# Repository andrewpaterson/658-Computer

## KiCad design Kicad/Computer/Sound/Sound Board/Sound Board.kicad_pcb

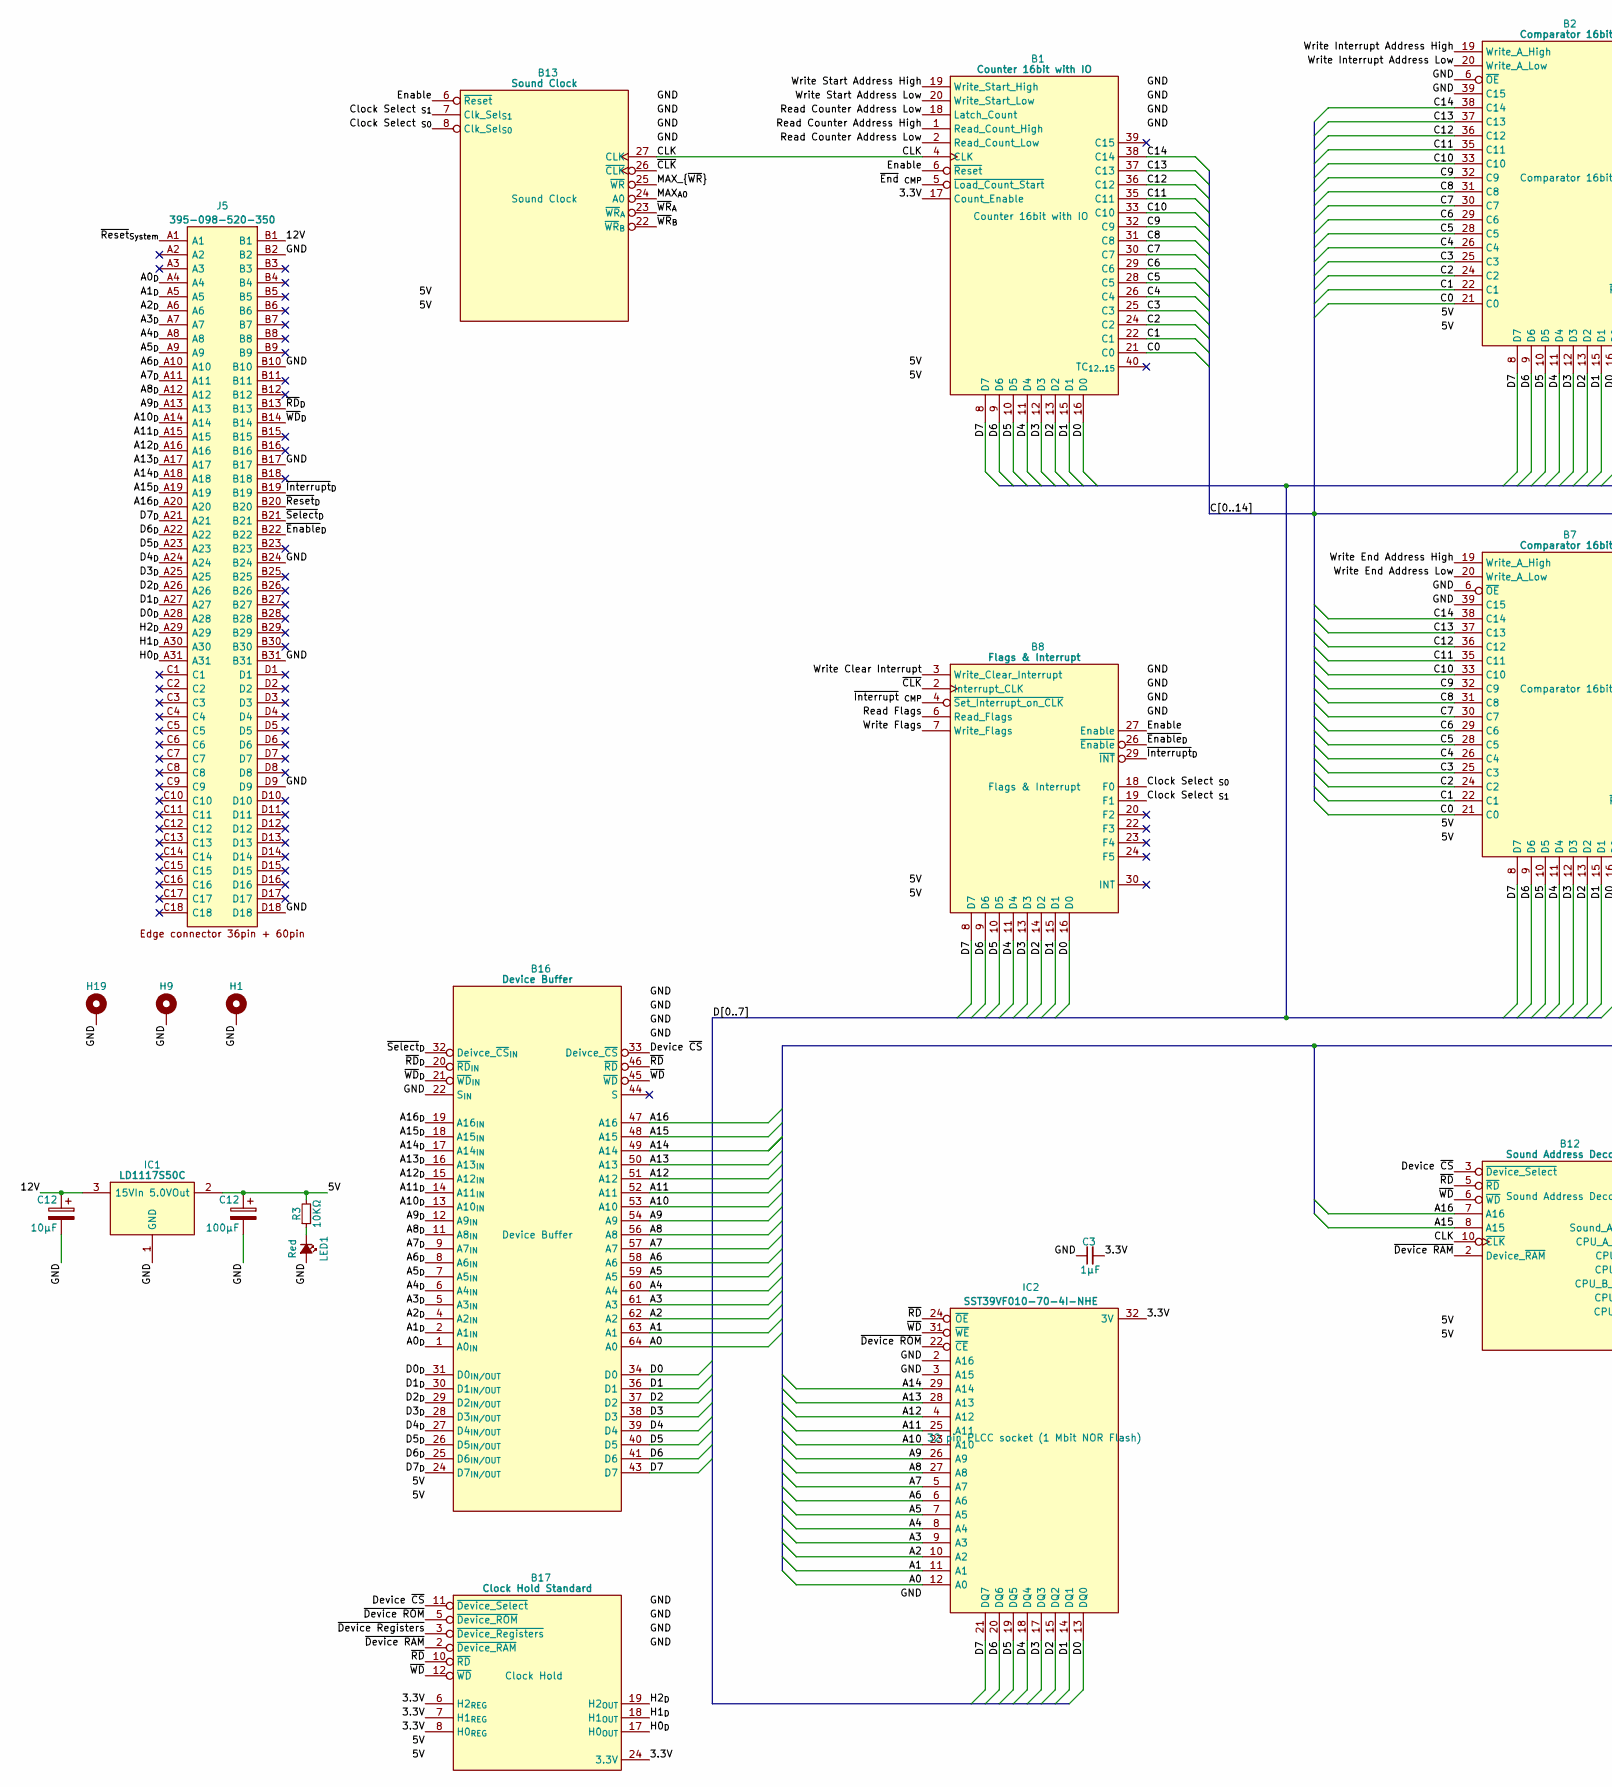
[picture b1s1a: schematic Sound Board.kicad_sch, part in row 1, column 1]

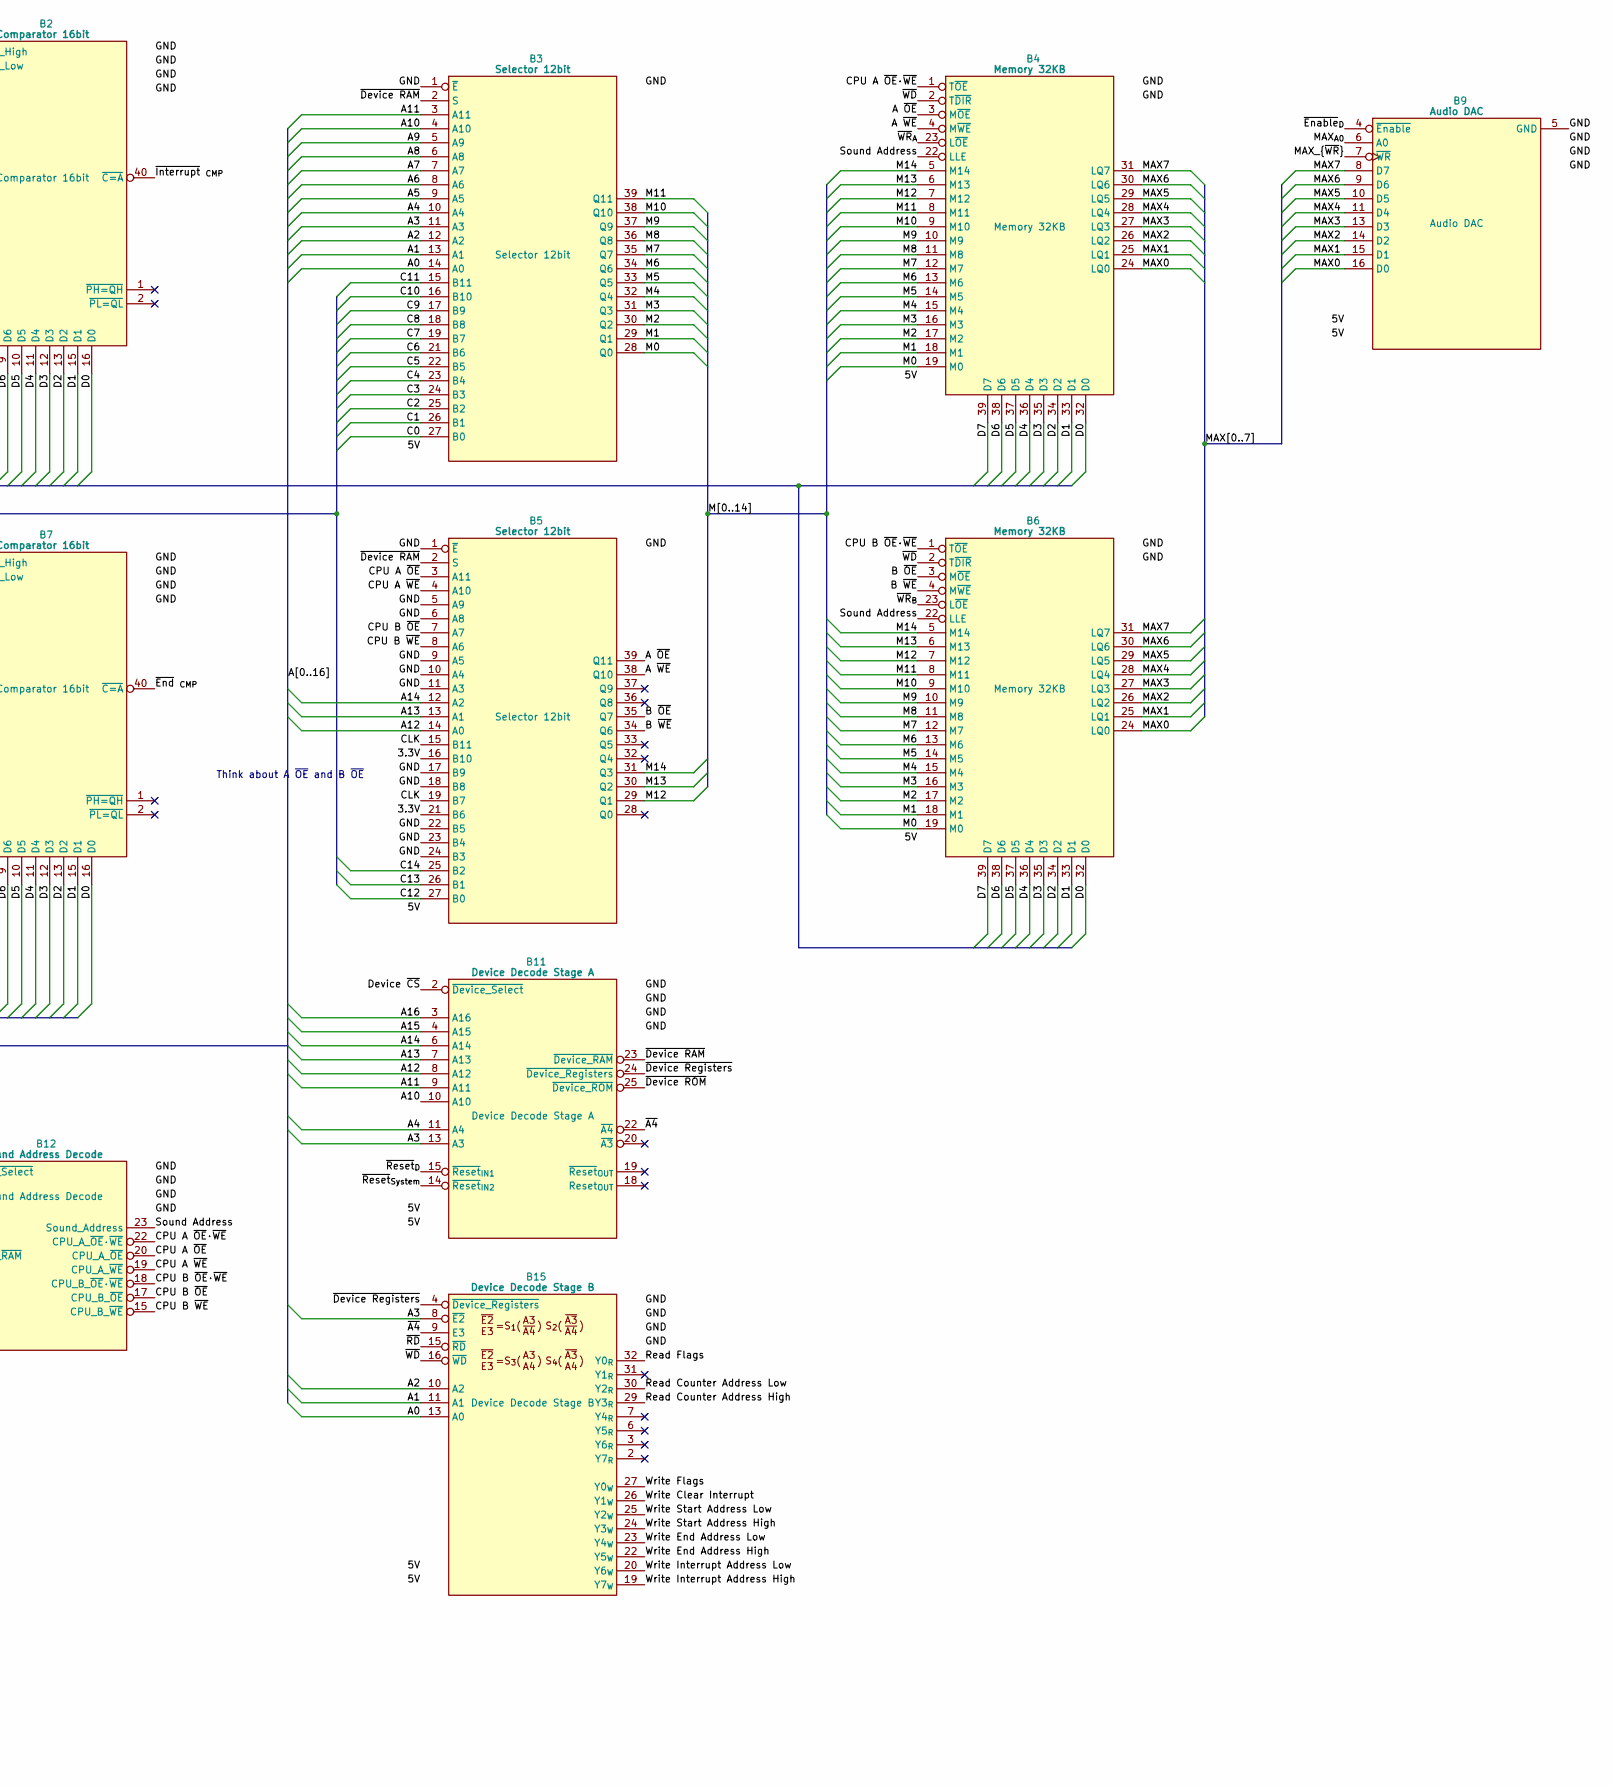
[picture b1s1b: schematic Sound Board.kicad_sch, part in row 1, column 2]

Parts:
B1: Counter 16bit with IO; HCP65_Counter_16bit_DIO
B2, B7: Comparator 16bit; HCP65_Comparator_16bit
B3, B5: Selector 12bit; HCP65_Selector_12bit
B4, B6: Memory 32KB; HCP65_Memory_32KB_With_Latch
B8: Flags & Interrupt; HCP65_Flags_Interrupt
B9: Audio DAC; HCP65_Audio_DAC
B11: Device Decode Stage A; HCP65_Device_Decode_Stage_A
B12: Sound Address Decode; HCP65_Sound_Address_Decode
B13: Sound Clock; HCP65_Sound_Clock
B15: Device Decode Stage B; HCP65_Device_Decode_Stage_B
B16: Device Buffer; HCP65_Device_Buffer
B17: Clock Hold Standard; HCP65_Clock_Hold_Standard
C3: 1μF; C_0805
C12: 10μF; CP_Radial_D4.0mm_P2.00mm
H1, H9, H19: MountingHole_Pad; HCP65_MountingHole_M3_
IC1: LD1117S50C; LD1117S33C; Manufacturer_Part_Number LD1117S50C
IC2: SST39VF010-70-4I-NHE; 5408803224008; Manufacturer_Part_Number SST39VF010-70-4I-NHE
J5: 395-098-520-350; 98pin Edge Connector; Manufacturer_Part_Number 395-098-520-350; Mouser Part Number 587-395-098-520-350
LED1: Red; LED_D5.0mm
R3: 10KΩ; R_0805

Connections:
/3.3V: B1.17 (Count_Enable), B5.16 (B10), B5.21 (B6), B17.6 (H2_{REG}), B17.7 (H1_{REG}), B17.8 (H0_{REG}), B17.24 (3.3V), C3.2, IC2.32 (3V)
/5V: B1.3 (5V), B1.23 (5V), B2.3 (5V), B2.23 (5V), B3.20 (5V), B4.20 (5V), B5.20 (5V), B6.20 (5V), B7.3 (5V), B7.23 (5V), B8.1 (5V), B8.17 (5V), B9.1 (5V), B9.17 (5V), B11.1 (5V), B11.17 (5V), B12.1 (5V), B12.13 (5V), B13.1 (5V), B13.17 (5V), B15.1 (5V), B15.17 (5V), B16.3 (5V), B16.35 (5V), B17.1 (5V), B17.13 (5V), IC1.2 (5.0VOut); also elsewhere on the board
/12V: IC1.3 (15VIn), J5.B1; also elsewhere on the board
/A0: B3.14 (A0), B15.13 (A0), B16.64 (A0), IC2.12 (A0)
/A0_{D}: B16.1 (A0_{IN}), J5.A4
/A1: B3.13 (A1), B15.11 (A1), B16.63 (A1), IC2.11 (A1)
/A1_{D}: B16.2 (A1_{IN}), J5.A5
/A2: B3.12 (A2), B15.10 (A2), B16.62 (A2), IC2.10 (A2)
/A2_{D}: B16.4 (A2_{IN}), J5.A6
/A3: B3.11 (A3), B11.13 (A3), B15.8 (~E2), B16.61 (A3), IC2.9 (A3)
/A3_{D}: B16.5 (A3_{IN}), J5.A7
/A4: B3.10 (A4), B11.11 (A4), B16.60 (A4), IC2.8 (A4)
/A4_{D}: B16.6 (A4_{IN}), J5.A8
/A5: B3.9 (A5), B16.59 (A5), IC2.7 (A5)
/A5_{D}: B16.7 (A5_{IN}), J5.A9
/A6: B3.8 (A6), B16.58 (A6), IC2.6 (A6)
/A6_{D}: B16.8 (A6_{IN}), J5.A10
/A7: B3.7 (A7), B16.57 (A7), IC2.5 (A7)
/A7_{D}: B16.9 (A7_{IN}), J5.A11
/A8: B3.6 (A8), B16.56 (A8), IC2.27 (A8)
/A8_{D}: B16.11 (A8_{IN}), J5.A12
/A9: B3.5 (A9), B16.54 (A9), IC2.26 (A9)
/A9_{D}: B16.12 (A9_{IN}), J5.A13
/A10: B3.4 (A10), B11.10 (A10), B16.53 (A10), IC2.23 (A10)
/A10_{D}: B16.13 (A10_{IN}), J5.A14
/A11: B3.3 (A11), B11.9 (A11), B16.52 (A11), IC2.25 (A11)
/A11_{D}: B16.14 (A11_{IN}), J5.A15
/A12: B5.14 (A0), B11.8 (A12), B16.51 (A12), IC2.4 (A12)
/A12_{D}: B16.15 (A12_{IN}), J5.A16
/A13: B5.13 (A1), B11.7 (A13), B16.50 (A13), IC2.28 (A13)
/A13_{D}: B16.16 (A13_{IN}), J5.A17
/A14: B5.12 (A2), B11.6 (A14), B16.49 (A14), IC2.29 (A14)
/A14_{D}: B16.17 (A14_{IN}), J5.A18
/A15: B11.4 (A15), B12.8 (A15), B16.48 (A15)
/A15_{D}: B16.18 (A15_{IN}), J5.A19
/A16: B11.3 (A16), B12.7 (A16), B16.47 (A16)
/A16_{D}: B16.19 (A16_{IN}), J5.A20
/A ~OE: B4.3 (M~OE), B5.39 (Q11)
/A ~WE: B4.4 (M~WE), B5.38 (Q10)
/B ~OE: B5.35 (Q7), B6.3 (M~OE)
/B ~WE: B5.34 (Q6), B6.4 (M~WE)
/C0: B1.21 (C0), B2.21 (C0), B3.27 (B0), B7.21 (C0)
/C1: B1.22 (C1), B2.22 (C1), B3.26 (B1), B7.22 (C1)
/C2: B1.24 (C2), B2.24 (C2), B3.25 (B2), B7.24 (C2)
/C3: B1.25 (C3), B2.25 (C3), B3.24 (B3), B7.25 (C3)
/C4: B1.26 (C4), B2.26 (C4), B3.23 (B4), B7.26 (C4)
/C5: B1.28 (C5), B2.28 (C5), B3.22 (B5), B7.28 (C5)
/C6: B1.29 (C6), B2.29 (C6), B3.21 (B6), B7.29 (C6)
/C7: B1.30 (C7), B2.30 (C7), B3.19 (B7), B7.30 (C7)
/C8: B1.31 (C8), B2.31 (C8), B3.18 (B8), B7.31 (C8)
/C9: B1.32 (C9), B2.32 (C9), B3.17 (B9), B7.32 (C9)
/C10: B1.33 (C10), B2.33 (C10), B3.16 (B10), B7.33 (C10)
/C11: B1.35 (C11), B2.35 (C11), B3.15 (B11), B7.35 (C11)
/C12: B1.36 (C12), B2.36 (C12), B5.27 (B0), B7.36 (C12)
/C13: B1.37 (C13), B2.37 (C13), B5.26 (B1), B7.37 (C13)
/C14: B1.38 (C14), B2.38 (C14), B5.25 (B2), B7.38 (C14)
/CLK: B1.4 (CLK), B5.15 (B11), B5.19 (B7), B12.10 (~CLK), B13.27 (CLK)
/CPU A ~OE: B5.3 (A11), B12.20 (CPU_A_~OE)
/CPU A ~OE·~WE: B4.1 (T~OE), B12.22 (CPU_A_~OE·~WE)
/CPU A ~WE: B5.4 (A10), B12.19 (CPU_A_~WE)
/CPU B ~OE: B5.7 (A7), B12.17 (CPU_B_~OE)
/CPU B ~OE·~WE: B6.1 (T~OE), B12.18 (CPU_B_~OE·~WE)
/CPU B ~WE: B5.8 (A6), B12.15 (CPU_B_~WE)
/Clock Select _{S0}: B8.18 (F0), B13.8 (Clk_Sel_{S0})
/Clock Select _{S1}: B8.19 (F1), B13.7 (Clk_Sel_{S1})
/D0: B1.16 (D0), B2.16 (D0), B4.32 (D0), B6.32 (D0), B7.16 (D0), B8.16 (D0), B16.34 (D0), IC2.13 (DQ0)
/D0_{D}: B16.31 (D0_{IN/OUT}), J5.A28
/D1: B1.15 (D1), B2.15 (D1), B4.33 (D1), B6.33 (D1), B7.15 (D1), B8.15 (D1), B16.36 (D1), IC2.14 (DQ1)
/D1_{D}: B16.30 (D1_{IN/OUT}), J5.A27
/D2: B1.13 (D2), B2.13 (D2), B4.34 (D2), B6.34 (D2), B7.13 (D2), B8.14 (D2), B16.37 (D2), IC2.15 (DQ2)
/D2_{D}: B16.29 (D2_{IN/OUT}), J5.A26
/D3: B1.12 (D3), B2.12 (D3), B4.35 (D3), B6.35 (D3), B7.12 (D3), B8.13 (D3), B16.38 (D3), IC2.17 (DQ3)
/D3_{D}: B16.28 (D3_{IN/OUT}), J5.A25
/D4: B1.11 (D4), B2.11 (D4), B4.36 (D4), B6.36 (D4), B7.11 (D4), B8.11 (D4), B16.39 (D4), IC2.18 (DQ4)
/D4_{D}: B16.27 (D4_{IN/OUT}), J5.A24
/D5: B1.10 (D5), B2.10 (D5), B4.37 (D5), B6.37 (D5), B7.10 (D5), B8.10 (D5), B16.40 (D5), IC2.19 (DQ5)
/D5_{D}: B16.26 (D5_{IN/OUT}), J5.A23
/D6: B1.9 (D6), B2.9 (D6), B4.38 (D6), B6.38 (D6), B7.9 (D6), B8.9 (D6), B16.41 (D6), IC2.20 (DQ6)
/D6_{D}: B16.25 (D6_{IN/OUT}), J5.A22
/D7: B1.8 (D7), B2.8 (D7), B4.39 (D7), B6.39 (D7), B7.8 (D7), B8.8 (D7), B16.43 (D7), IC2.21 (DQ7)
/D7_{D}: B16.24 (D7_{IN/OUT}), J5.A21
/Device ~CS: B11.2 (~Device_Select), B12.3 (~Device_Select), B16.33 (Deivce_~CS), B17.11 (~Device_Select)
/Enable: B1.6 (~Reset), B8.27 (Enable), B13.6 (~Reset)
/GND: B1.7 (GND), B1.14 (GND), B1.27 (GND), B1.34 (GND), B2.6 (~OE), B2.7 (GND), B2.14 (GND), B2.27 (GND), B2.34 (GND), B2.39 (C15), B3.1 (~E), B3.40 (GND), B4.21 (GND), B4.40 (GND), B5.1 (~E), B5.5 (A9), B5.6 (A8), B5.9 (A5), B5.10 (A4), B5.11 (A3), B5.17 (B9), B5.18 (B8), B5.22 (B5), B5.23 (B4), B5.24 (B3), B5.40 (GND), B6.21 (GND), B6.40 (GND), B7.6 (~OE), B7.7 (GND), B7.14 (GND), B7.27 (GND), B7.34 (GND), B7.39 (C15), B8.5 (GND), B8.12 (GND), B8.21 (GND), B8.28 (GND), B9.5 (GND), B9.12 (GND), B9.21 (GND), B9.28 (GND), B11.5 (GND), B11.12 (GND), B11.21 (GND), B11.28 (GND), B12.4 (GND), B12.9 (GND), B12.16 (GND), B12.21 (GND), B13.5 (GND), B13.12 (GND), B13.21 (GND), B13.28 (GND), B15.5 (GND), B15.12 (GND), B15.21 (GND), B15.28 (GND), B16.10 (GND), B16.22 (S_{IN}), B16.23 (GND), B16.42 (GND), B16.55 (GND), B17.4 (GND), B17.9 (GND), B17.16 (GND), B17.21 (GND), C3.1, H1.1 (GND), H9.1 (GND), H19.1 (GND), IC1.1 (GND), IC2.2 (A16), IC2.3 (A15), IC2.16 (GND), J5.B2, J5.B10, J5.B17, J5.B24, J5.B31, J5.D9, J5.D18, LED1.2 (A); also elsewhere on the board
/H0_{D}: B17.17 (H0_{OUT}), J5.A31
/H1_{D}: B17.18 (H1_{OUT}), J5.A30
/H2_{D}: B17.19 (H2_{OUT}), J5.A29
/M0: B3.28 (Q0), B4.19 (M0), B6.19 (M0)
/M1: B3.29 (Q1), B4.18 (M1), B6.18 (M1)
/M2: B3.30 (Q2), B4.17 (M2), B6.17 (M2)
/M3: B3.31 (Q3), B4.16 (M3), B6.16 (M3)
/M4: B3.32 (Q4), B4.15 (M4), B6.15 (M4)
/M5: B3.33 (Q5), B4.14 (M5), B6.14 (M5)
/M6: B3.34 (Q6), B4.13 (M6), B6.13 (M6)
/M7: B3.35 (Q7), B4.12 (M7), B6.12 (M7)
/M8: B3.36 (Q8), B4.11 (M8), B6.11 (M8)
/M9: B3.37 (Q9), B4.10 (M9), B6.10 (M9)
/M10: B3.38 (Q10), B4.9 (M10), B6.9 (M10)
/M11: B3.39 (Q11), B4.8 (M11), B6.8 (M11)
/M12: B4.7 (M12), B5.29 (Q1), B6.7 (M12)
/M13: B4.6 (M13), B5.30 (Q2), B6.6 (M13)
/M14: B4.5 (M14), B5.31 (Q3), B6.5 (M14)
/MAX0: B4.24 (LQ0), B6.24 (LQ0), B9.16 (D0)
/MAX1: B4.25 (LQ1), B6.25 (LQ1), B9.15 (D1)
/MAX2: B4.26 (LQ2), B6.26 (LQ2), B9.14 (D2)
/MAX3: B4.27 (LQ3), B6.27 (LQ3), B9.13 (D3)
/MAX4: B4.28 (LQ4), B6.28 (LQ4), B9.11 (D4)
/MAX5: B4.29 (LQ5), B6.29 (LQ5), B9.10 (D5)
/MAX6: B4.30 (LQ6), B6.30 (LQ6), B9.9 (D6)
/MAX7: B4.31 (LQ7), B6.31 (LQ7), B9.8 (D7)
/MAX_{A0}: B9.6 (A0), B13.24 (A0)
/MAX_{~WR}: B9.7 (~WR), B13.25 (~WR)
/Read Counter Address High: B1.1 (Read_Count_High), B15.29 (Y3_{R})
/Read Counter Address Low: B1.2 (Read_Count_Low), B1.18 (Latch_Count), B15.30 (Y2_{R})
/Read Flags: B8.6 (Read_Flags), B15.32 (Y0_{R})
/Sound Address: B4.22 (LLE), B6.22 (LLE), B12.23 (Sound_Address)
/Write Clear Interrupt: B8.3 (Write_Clear_Interrupt), B15.26 (Y1_{W})
/Write End Address High: B7.19 (Write_A_High), B15.22 (Y5_{W})
/Write End Address Low: B7.20 (Write_A_Low), B15.23 (Y4_{W})
/Write Flags: B8.7 (Write_Flags), B15.27 (Y0_{W})
/Write Interrupt Address High: B2.19 (Write_A_High), B15.19 (Y7_{W})
/Write Interrupt Address Low: B2.20 (Write_A_Low), B15.20 (Y6_{W})
/Write Start Address High: B1.19 (Write_Start_High), B15.24 (Y3_{W})
/Write Start Address Low: B1.20 (Write_Start_Low), B15.25 (Y2_{W})
/~A4: B11.22 (~A4), B15.9 (E3)
/~CLK: B8.2 (Interrupt_CLK), B13.26 (~CLK)
/~Device RAM: B3.2 (S), B5.2 (S), B11.23 (~Device_RAM), B12.2 (Device_~RAM), B17.2 (~Device_RAM)
/~Device ROM: B11.25 (~Device_ROM), B17.5 (~Device_ROM), IC2.22 (~CE)
/~Device Registers: B11.24 (~Device_Registers), B15.4 (~Device_Registers), B17.3 (~Device_Registers)
/~Enable_{D}: B8.26 (~Enable), B9.4 (~Enable), J5.B22
/~End _{CMP}: B1.5 (~Load_Count_Start), B7.40 (~C=A)
/~Interrupt _{CMP}: B2.40 (~C=A), B8.4 (~Set_Interrupt_on_CLK)
/~Interrupt_{D}: B8.29 (~INT), J5.B19
/~RD: B12.5 (~RD), B15.15 (~RD), B16.46 (~RD), B17.10 (~RD), IC2.24 (~OE)
/~RD_{D}: B16.20 (~RD_{IN}), J5.B13
/~Reset_{D}: B11.15 (~Reset_{IN1}), J5.B20
/~Reset_{System}: B11.14 (~Reset_{IN2}), J5.A1
/~Select_{D}: B16.32 (Deivce_~CS_{IN}), J5.B21
/~WD: B4.2 (T~DIR), B6.2 (T~DIR), B12.6 (~WD), B15.16 (~WD), B16.45 (~WD), B17.12 (~WD), IC2.31 (~WE)
/~WD_{D}: B16.21 (~WD_{IN}), J5.B14
/~WR_{A}: B4.23 (L~OE), B13.23 (~WR_{A})
/~WR_{B}: B6.23 (L~OE), B13.22 (~WR_{B})
unnamed 142: LED1.1 (K); also elsewhere on the board

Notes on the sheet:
Think about A ~{OE} and B ~{OE}

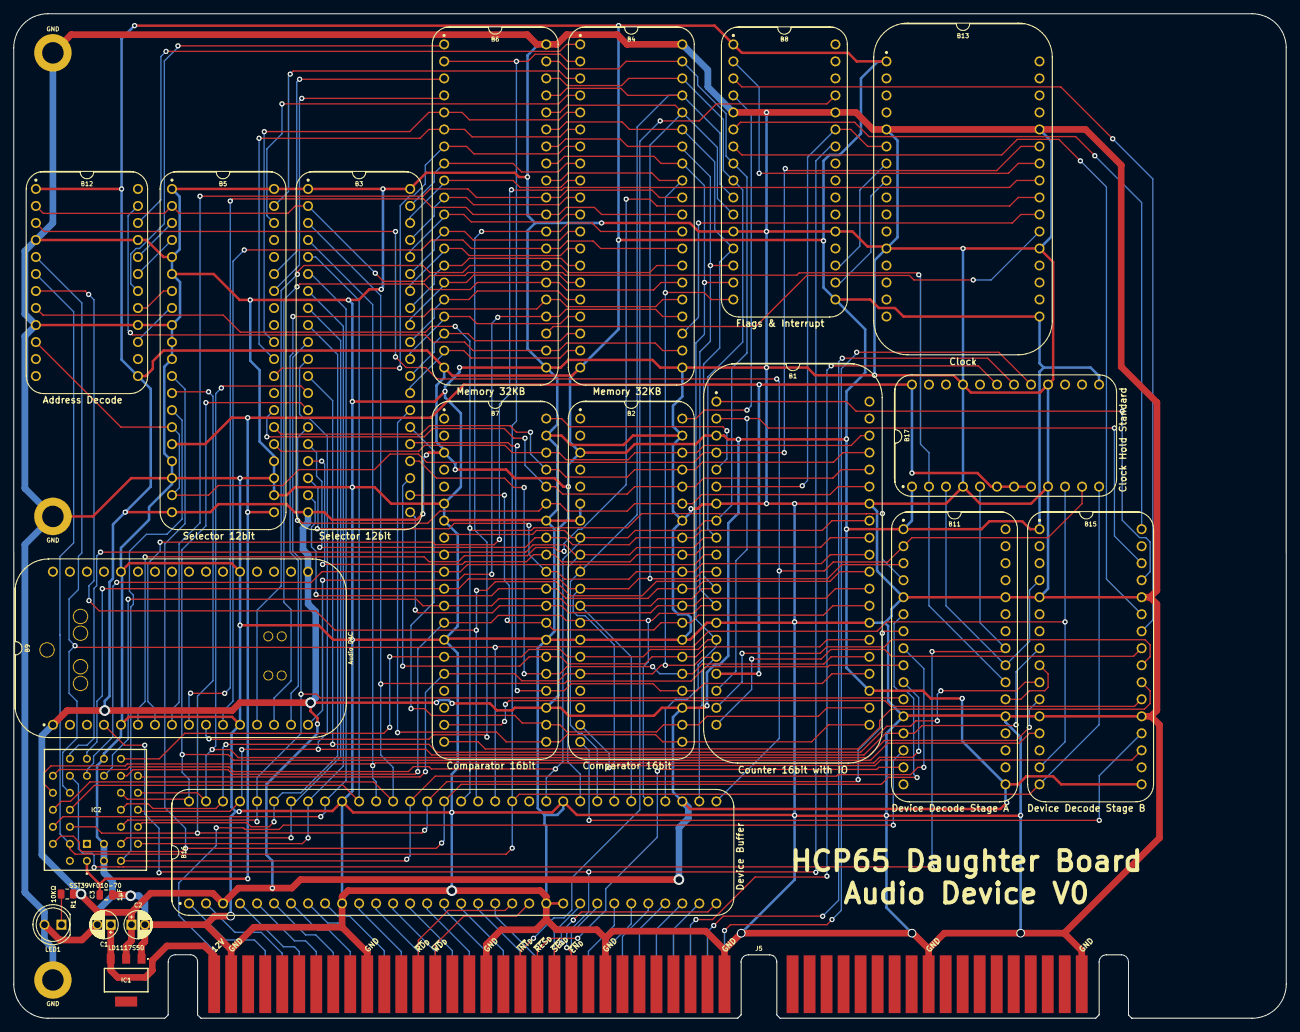
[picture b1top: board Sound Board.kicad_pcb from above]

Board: 2 copper layers, 190.0 x 150.0 mm, 26 parts (0 on the bottom side), 143 nets.

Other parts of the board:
C1: 10μF; CP_Radial_D4.0mm_P2.00mm
C2: 100μF; CP_Radial_D4.0mm_P2.00mm
R1: 10KΩ; R_0805

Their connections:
/5V: C2.1, R1.2; also elsewhere on the board
/12V: C1.1; also elsewhere on the board
/GND: C1.2, C2.2; also elsewhere on the board
unnamed 142: R1.1; also elsewhere on the board

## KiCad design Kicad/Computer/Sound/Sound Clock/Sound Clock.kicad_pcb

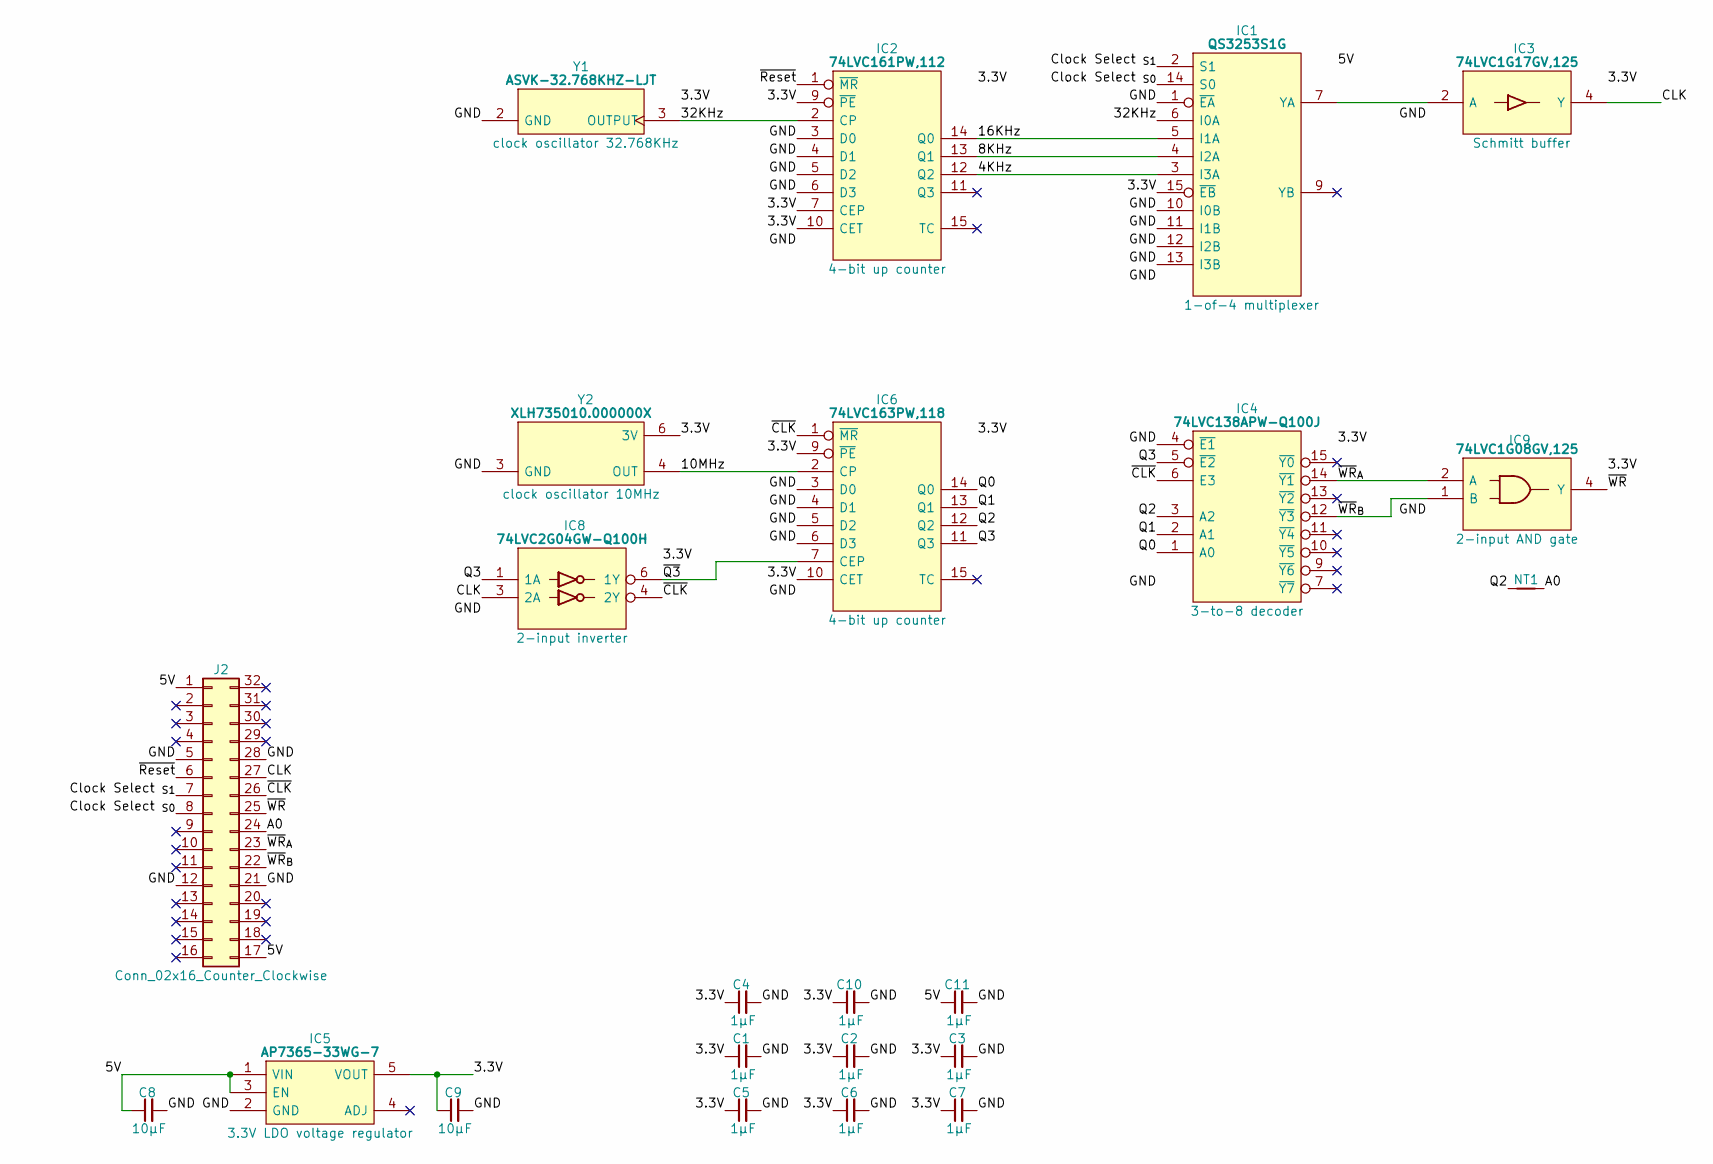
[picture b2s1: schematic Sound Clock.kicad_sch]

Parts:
C1, C2, C3, C4, C5, C6, C7, C10, C11: 1μF; C_0805
C8, C9: 10µF; C_0805
IC1: QS3253S1G; SOIC127P602X173-16N; Manufacturer_Part_Number QS3253S1G
IC2: 74LVC161PW,112; SOP65P640X110-16N; Mouser Part Number 771-LVC161PW112
IC3: 74LVC1G17GV,125; SOT95P275X110-5N; Manufacturer_Part_Number 74LVC1G17GV,125; Mouser Part Number 771-LVC1G17GV125
IC4: 74LVC138APW-Q100J; SOP65P640X110-16N; Mouser Part Number 771-74LVC138APWQ100J
IC5: AP7365-33WG-7; SOT95P285X130-5N; Manufacturer_Part_Number AP7365-33WG-7; Mouser Part Number 621-AP7365-33WG-7
IC6: 74LVC163PW,118; SOP65P640X110-16N; Mouser Part Number 771-74LVC163PW-T
IC8: 74LVC2G04GW-Q100H; SOP65P210X110-6N; Manufacturer_Part_Number 74LVC2G04GW-Q100H; Mouser Part Number 771-74LVC2G04GWQ100H
IC9: 74LVC1G08GV,125; SOT95P275X110-5N; Manufacturer_Part_Number 74LVC1G08GV,125; Mouser Part Number 771-74LVC1G08GV
J2: Conn_02x16_Counter_Clockwise; DIP-32_Board_W22.86mm
NT1: NetTie; NetTie-2_SMD_Pad0.5mm
Y1: ASVK-32.768KHZ-LJT; ASVK32768KHZLJT; Manufacturer_Part_Number ASVK-32.768KHZ-LJT; Mouser Part Number 815-ASVK-32.768KLJT
Y2: XLH735010.000000X; XLH735100000000I; Manufacturer_Part_Number XLH735010.000000X; Mouser Part Number 972-XLH735010000000X

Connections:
/3.3V: C1.1, C2.1, C3.1, C4.1, C5.1, C6.1, C7.1, C9.1, C10.1, IC1.15 (~EB), IC2.7 (CEP), IC2.9 (~PE), IC2.10 (CET), IC2.16 (3V), IC3.5 (3V), IC4.16 (3V), IC5.5 (VOUT), IC6.9 (~PE), IC6.10 (CET), IC6.16 (3V), IC8.5 (3V), IC9.5 (3V), Y1.4 (3V), Y2.6 (3V)
/4KHz: IC1.3 (I3A), IC2.12 (Q2)
/5V: C8.1, C11.1, IC1.16 (5V), IC5.1 (VIN), IC5.3 (EN), J2.1, J2.17
/8KHz: IC1.4 (I2A), IC2.13 (Q1)
/10MHz: IC6.2 (CP), Y2.4 (OUT)
/16KHz: IC1.5 (I1A), IC2.14 (Q0)
/32KHz: IC1.6 (I0A), IC2.2 (CP), Y1.3 (OUTPUT)
/A0: J2.24, NT1.2
/CLK: IC3.4 (Y), IC8.3 (2A), J2.27
/Clock Select _{S0}: IC1.14 (S0), J2.8
/Clock Select _{S1}: IC1.2 (S1), J2.7
/GND: C1.2, C2.2, C3.2, C4.2, C5.2, C6.2, C7.2, C8.2, C9.2, C10.2, C11.2, IC1.1 (~EA), IC1.8 (GND), IC1.10 (I0B), IC1.11 (I1B), IC1.12 (I2B), IC1.13 (I3B), IC2.3 (D0), IC2.4 (D1), IC2.5 (D2), IC2.6 (D3), IC2.8 (GND), IC3.3 (GND), IC4.4 (~E1), IC4.8 (GND), IC5.2 (GND), IC6.3 (D0), IC6.4 (D1), IC6.5 (D2), IC6.6 (D3), IC6.8 (GND), IC8.2 (GND), IC9.3 (GND), J2.5, J2.12, J2.21, J2.28, Y1.2 (GND), Y2.3 (GND)
/Q0: IC4.1 (A0), IC6.14 (Q0)
/Q1: IC4.2 (A1), IC6.13 (Q1)
/Q2: IC4.3 (A2), IC6.12 (Q2), NT1.1
/Q3: IC4.5 (~E2), IC6.11 (Q3), IC8.1 (1A)
/~CLK: IC4.6 (E3), IC6.1 (~MR), IC8.4 (2Y), J2.26
/~Q3: IC6.7 (CEP), IC8.6 (1Y)
/~Reset: IC2.1 (~MR), J2.6
/~WR: IC9.4 (Y), J2.25
/~WR_{A}: IC4.14 (~Y1), IC9.2 (A), J2.23
/~WR_{B}: IC4.12 (~Y3), IC9.1 (B), J2.22
unnamed: IC1.7 (YA), IC3.2 (A)

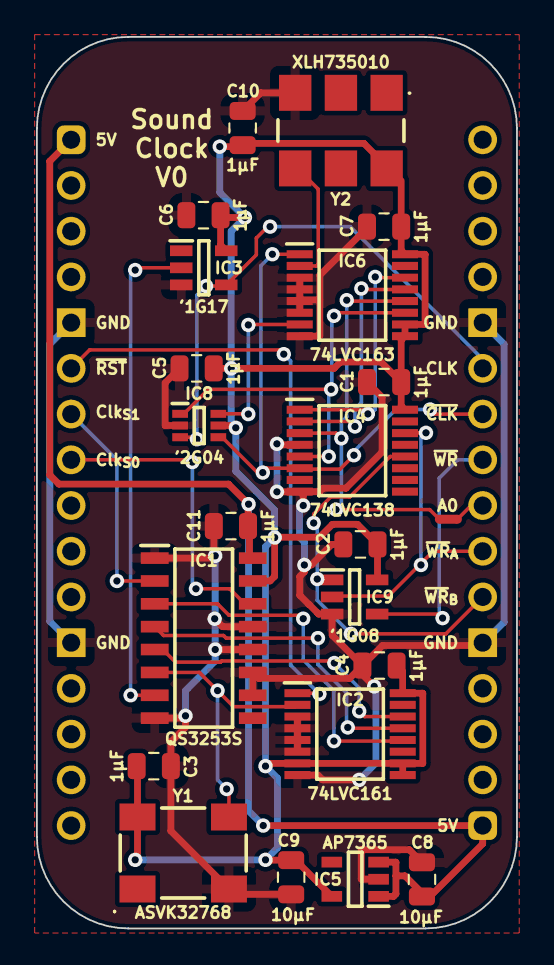
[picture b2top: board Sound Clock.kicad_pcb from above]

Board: 2 copper layers, 26.7 x 49.5 mm, 23 parts (0 on the bottom side), 23 nets.

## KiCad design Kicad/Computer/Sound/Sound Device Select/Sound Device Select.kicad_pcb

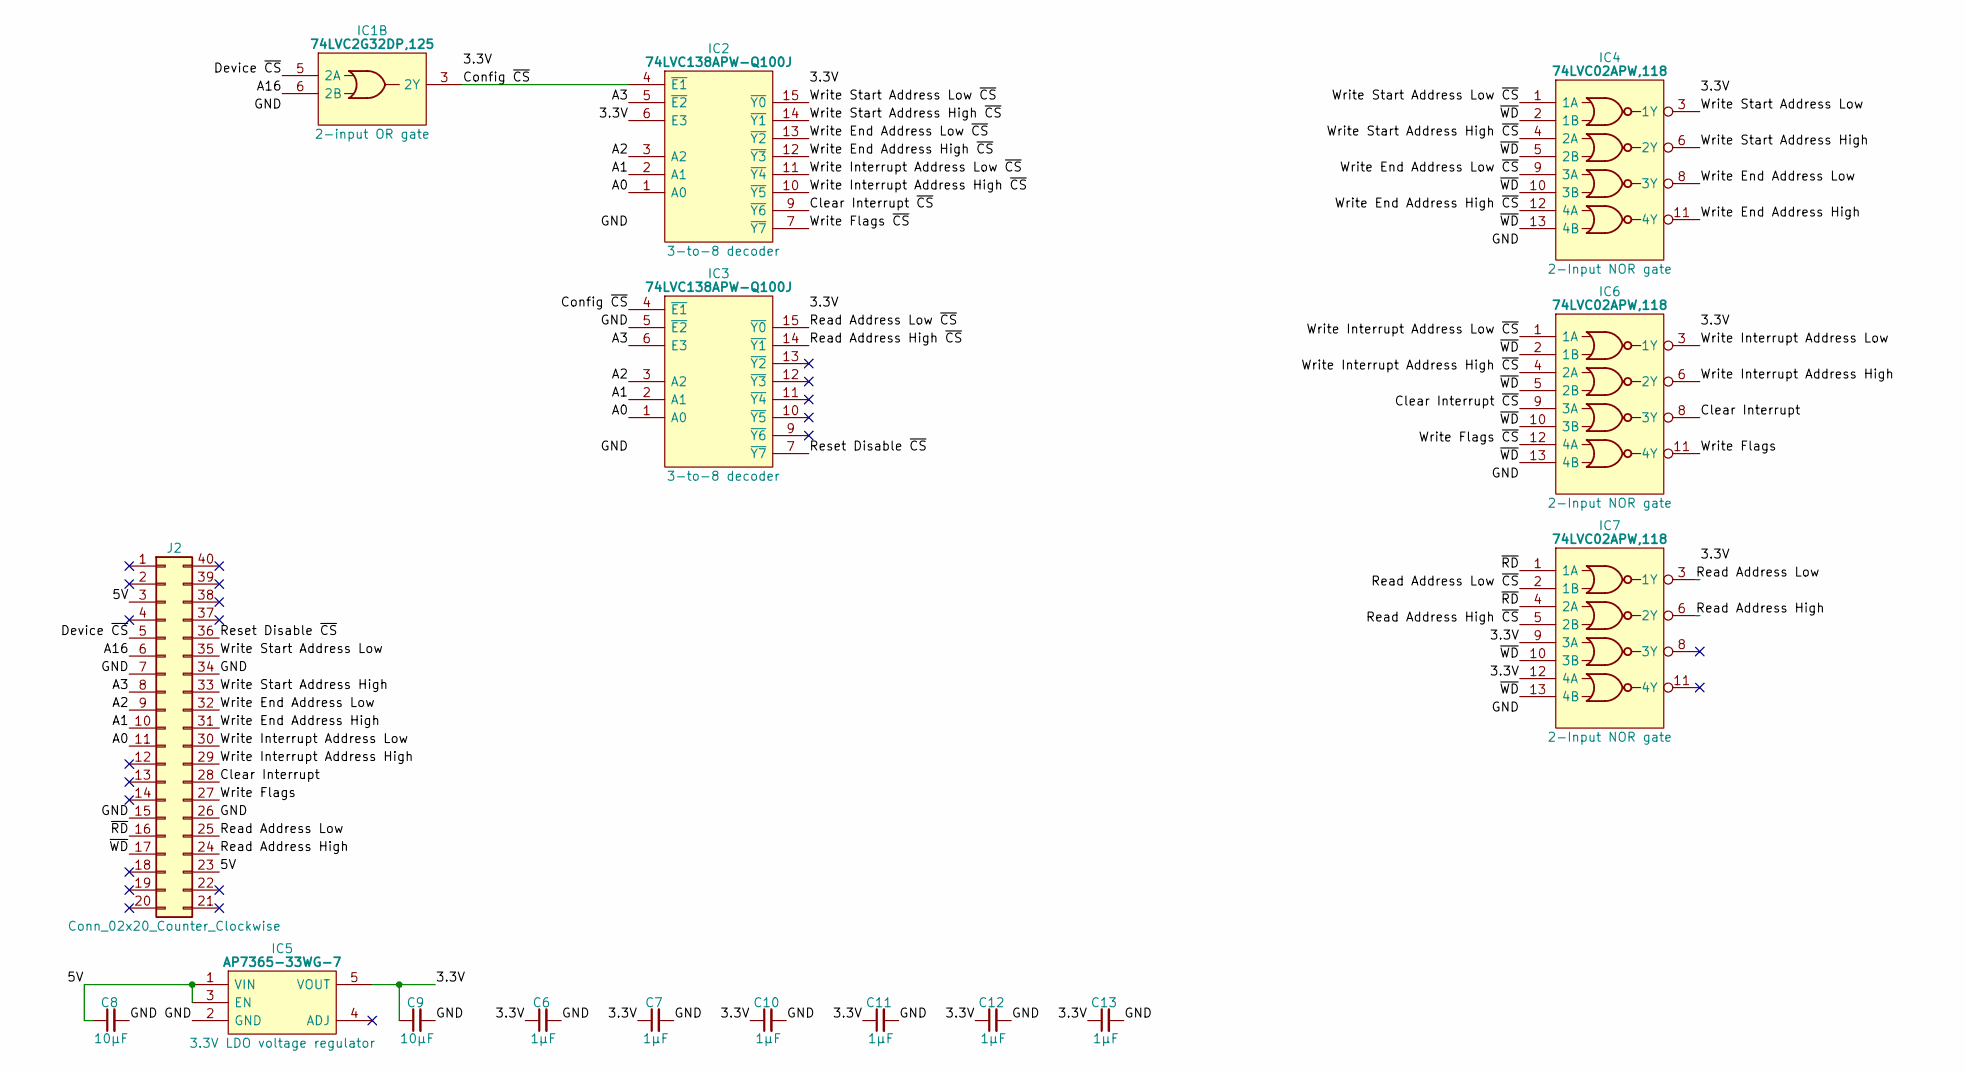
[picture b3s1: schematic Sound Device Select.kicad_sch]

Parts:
C6, C7, C10, C11, C12, C13: 1μF; C_0805
C8, C9: 10µF; C_0805
IC1: 74LVC2G32DP,125; SOP65P400X110-8N; Manufacturer_Part_Number 74LVC2G32DP,125; Mouser Part Number 771-LVC2G32DP125
IC2, IC3: 74LVC138APW-Q100J; SOP65P640X110-16N; Mouser Part Number 771-74LVC138APWQ100J
IC4, IC6, IC7: 74LVC02APW,118; SOP65P640X110-14N; Mouser Part Number 771-74LVC02APW-T
IC5: AP7365-33WG-7; SOT95P285X130-5N; Manufacturer_Part_Number AP7365-33WG-7; Mouser Part Number 621-AP7365-33WG-7
J2: Conn_02x20_Counter_Clockwise; DIP-40_Board_W15.24mm

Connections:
/3.3V: C6.1, C7.1, C9.1, C10.1, C11.1, C12.1, C13.1, IC1.8 (VCC), IC2.6 (E3), IC2.16 (3V), IC3.16 (3V), IC4.14 (3V), IC5.5 (VOUT), IC6.14 (3V), IC7.9 (3A), IC7.12 (4A), IC7.14 (3V)
/5V: C8.1, IC5.1 (VIN), IC5.3 (EN), J2.3, J2.23
/A0: IC2.1 (A0), IC3.1 (A0), J2.11
/A1: IC2.2 (A1), IC3.2 (A1), J2.10
/A2: IC2.3 (A2), IC3.3 (A2), J2.9
/A3: IC2.5 (~E2), IC3.6 (E3), J2.8
/A16: IC1.6 (2B), J2.6
/Clear Interrupt: IC6.8 (3Y), J2.28
/Clear Interrupt ~CS: IC2.9 (~Y6), IC6.9 (3A)
/Config ~CS: IC1.3 (2Y), IC2.4 (~E1), IC3.4 (~E1)
/Device ~CS: IC1.5 (2A), J2.5
/GND: C6.2, C7.2, C8.2, C9.2, C10.2, C11.2, C12.2, C13.2, IC1.4 (GND), IC2.8 (GND), IC3.5 (~E2), IC3.8 (GND), IC4.7 (GND), IC5.2 (GND), IC6.7 (GND), IC7.7 (GND), J2.7, J2.15, J2.26, J2.34
/Read Address High: IC7.6 (2Y), J2.24
/Read Address High ~CS: IC3.14 (~Y1), IC7.5 (2B)
/Read Address Low: IC7.3 (1Y), J2.25
/Read Address Low ~CS: IC3.15 (~Y0), IC7.2 (1B)
/Reset Disable ~CS: IC3.7 (~Y7), J2.36
/Write End Address High: IC4.11 (4Y), J2.31
/Write End Address High ~CS: IC2.12 (~Y3), IC4.12 (4A)
/Write End Address Low: IC4.8 (3Y), J2.32
/Write End Address Low ~CS: IC2.13 (~Y2), IC4.9 (3A)
/Write Flags: IC6.11 (4Y), J2.27
/Write Flags ~CS: IC2.7 (~Y7), IC6.12 (4A)
/Write Interrupt Address High: IC6.6 (2Y), J2.29
/Write Interrupt Address High ~CS: IC2.10 (~Y5), IC6.4 (2A)
/Write Interrupt Address Low: IC6.3 (1Y), J2.30
/Write Interrupt Address Low ~CS: IC2.11 (~Y4), IC6.1 (1A)
/Write Start Address High: IC4.6 (2Y), J2.33
/Write Start Address High ~CS: IC2.14 (~Y1), IC4.4 (2A)
/Write Start Address Low: IC4.3 (1Y), J2.35
/Write Start Address Low ~CS: IC2.15 (~Y0), IC4.1 (1A)
/~RD: IC7.1 (1A), IC7.4 (2A), J2.16
/~WD: IC4.2 (1B), IC4.5 (2B), IC4.10 (3B), IC4.13 (4B), IC6.2 (1B), IC6.5 (2B), IC6.10 (3B), IC6.13 (4B), IC7.10 (3B), IC7.13 (4B), J2.17

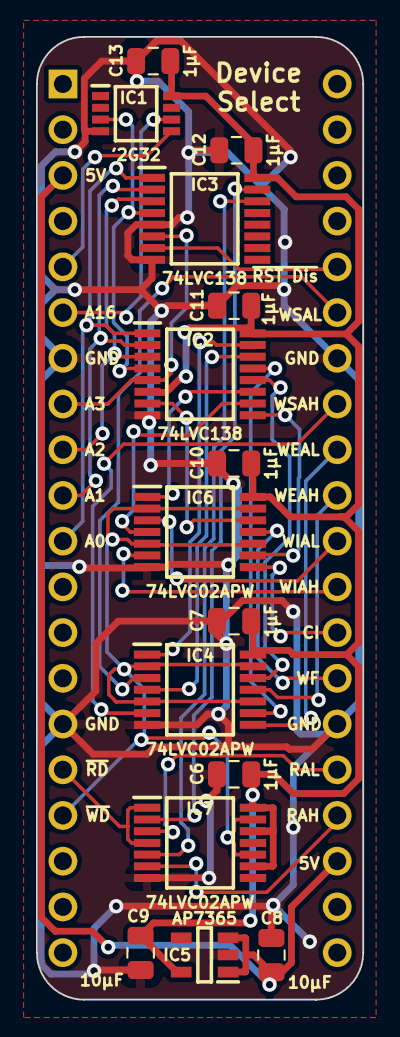
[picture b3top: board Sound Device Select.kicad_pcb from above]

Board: 2 copper layers, 18.1 x 53.5 mm, 16 parts (0 on the bottom side), 33 nets.
